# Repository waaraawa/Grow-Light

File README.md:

# Grow Light

A circular 12 V LED board designed for growing plants. The board uses a single-sided, 80 mm aluminum MCPCB with 20 red LEDs and 3 blue LEDs. A [medium Daiso aluminum makgeolli cup](https://www.daisomall.co.kr/pd/pdr/SCR_PDR_0001?pdNo=58656) serves as the heatsink and mechanical structure.

## Project Status

- Current KiCad design: `v1.0.3` (`2026-07-27`)
- Manufacturing order version: `v1.0.2` (`2026-07-11`)
- Current phase: `v1.0.2` assembled, functionally tested, and installed
- `v1.0.3` change: added `F.Silkscreen` guides around the six M3 mounting holes and the central cable hole
- Assembly note: the physical `v1.0.2` board currently uses a temporary hand-assembled resistor arrangement pending replacement with correctly sized `5025 Metric (2010 Imperial)` resistors
- DRC: 0 active errors, 0 active warnings, and 0 unconnected pads
- Exclusion: one warning for the unavailable source library of an embedded silkscreen graphic

> The design files in this repository are currently at `v1.0.3`. The previews below and the ordered MCPCB are `v1.0.2`. Manufacturing files for `v1.0.3` have not been generated.

## Specifications

| Item | Specification |
|---|---|
| PCB | 80 mm diameter, 1-layer Aluminum MCPCB |
| PCB thickness | 1.6 mm |
| Copper | 1 oz, `F.Cu` only |
| Surface finish | `HAL SnPb` |
| Solder mask / silkscreen | White / black, front side only |
| Power input | 12 V from a USB-C PD trigger board |
| Target power consumption | Approximately 2 W to 4 W |
| LEDs | 20 red and 3 blue |
| Resistors | Four 68 Ω and one 82 Ω, 2010 package |
| Track widths | 1.2 mm power tracks and 0.6 mm LED interconnects |
| Mounting holes | Six 3.2 mm M3 NPTH holes |
| Cable hole | One central 5.3 mm NPTH hole |

Because KiCad requires an even number of copper layers, the project represents the stackup as a 2-layer board. All electrical copper is on `F.Cu`; `B.Cu` is unused. The actual manufacturing structure is `F.Silkscreen / F.Mask / F.Cu / thermal dielectric / aluminum base`.

## Electrical Configuration

| Channel | LEDs per Series String | Parallel Strings | Total LEDs | String Resistor |
|---|---:|---:|---:|---:|
| Red | 5 | 4 | 20 | 68 Ω |
| Blue | 3 | 1 | 3 | 82 Ω |

The 2010 resistor bodies act as physical jumpers to complete the single-sided routing. Twenty-four `F.Cu` copper zones around the LEDs provide electrical connectivity and local heat spreading. The aluminum core is the primary thermal path, so the design does not use `B.Cu` heat-spreading copper or thermal vias.

## Design Images

### PCB Layout — v1.0.2

### Manufacturing Preview — v1.0.2

### Assembled Board Preview — v1.0.2

### Manufactured PCB

The physical `v1.0.2` aluminum MCPCB after delivery and initial inspection.

### Completed Assembly

The assembled light installed in its intended growing area.

See the [`v1.0.2` build log](docs/build-log-v1.0.2.md) for the complete assembly, hot-plate reflow, aluminum-cup drilling, thermal-interface, testing, and installation process.

## Assembly and Safety

- The red `IWS-L5056-UR-N3` and blue `IWS-L5056-UB-K3` LEDs use opposite footprint polarities. Verify every LED before placement.
- Do not rely on cable colors. Measure the 12 V output and polarity with a multimeter before soldering the cable to `J1 +12V` and `J2 GND`.
- Fit a grommet or strain relief where the cable passes through the central hole.
- Apply electrically non-conductive `UPSIREN UTP-8` in a thin, even layer between the PCB and the aluminum cup.
- Use insulating washers or nylon shoulder washers at the M3 mounting points.
- Before applying power and again after final assembly, verify that the aluminum structure and fasteners are not shorted to `+12V` or `GND`.
- The aluminum structure and external bracket, rather than the PCB, must carry the lamp's mechanical load.

## Repository Contents

- [`plant led.kicad_sch`](plant%20led.kicad_sch): schematic
- [`plant led.kicad_pcb`](plant%20led.kicad_pcb): PCB layout
- [`plant led.kicad_pro`](plant%20led.kicad_pro): KiCad project settings
- [`parts_list.md`](parts_list.md): parts, manufacturing, and assembly specifications
- [`to-do.md`](to-do.md): production, assembly, and test status
- [`docs/build-log-v1.0.2.md`](docs/build-log-v1.0.2.md): physical `v1.0.2` manufacturing, assembly, and installation log
- [`references/datasheets`](references/datasheets): LED datasheets

Manufacturing Gerber files are not included in the repository. The `footprints:` library is also stored in an external directory shared by multiple projects. To open the project in another environment, configure the same shared library path.

## License

This project is licensed under the [MIT License](LICENSE).

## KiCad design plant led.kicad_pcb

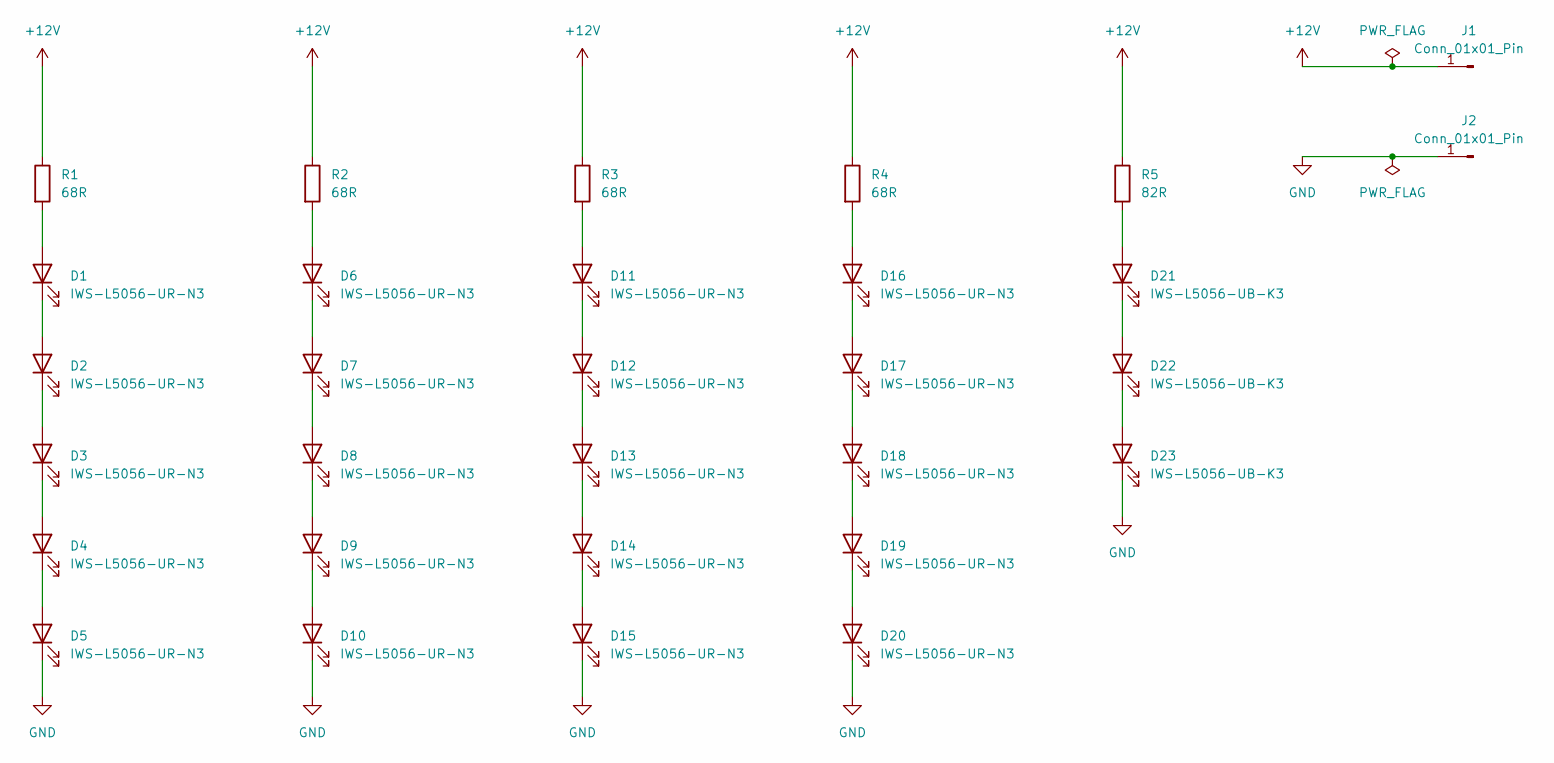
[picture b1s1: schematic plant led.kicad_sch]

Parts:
D1, D2, D3, D4, D5, D6, D7, D8, D9, D10, D11, D12, D13, D14, D15, D16, D17, D18, D19, D20: IWS-L5056-UR-N3; LED_5050_IWS_L5056_UR_N3
D21, D22, D23: IWS-L5056-UB-K3; LED_5050_IWS_L5056_UB_K3
J1, J2: Conn_01x01_Pin; Power_Solder_Pads_1P
R1, R2, R3, R4: 68R; R_2010_5025Metric
R5: 82R; R_2010_5025Metric

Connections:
+12V: J1.1 (Pin_1_1), R1.1, R2.1, R3.1, R4.1, R5.1
GND: D5.1 (K), D10.1 (K), D15.1 (K), D20.1 (K), D23.1 (K), J2.1 (Pin_1_1)
unnamed: D1.2 (A), R1.2
unnamed: D1.1 (K), D2.2 (A)
unnamed: D2.1 (K), D3.2 (A)
unnamed: D3.1 (K), D4.2 (A)
unnamed: D4.1 (K), D5.2 (A)
unnamed: D6.2 (A), R2.2
unnamed: D6.1 (K), D7.2 (A)
unnamed: D7.1 (K), D8.2 (A)
unnamed: D8.1 (K), D9.2 (A)
unnamed: D9.1 (K), D10.2 (A)
unnamed: D11.2 (A), R3.2
unnamed: D11.1 (K), D12.2 (A)
unnamed: D12.1 (K), D13.2 (A)
unnamed: D13.1 (K), D14.2 (A)
unnamed: D14.1 (K), D15.2 (A)
unnamed: D16.2 (A), R4.2
unnamed: D16.1 (K), D17.2 (A)
unnamed: D17.1 (K), D18.2 (A)
unnamed: D18.1 (K), D19.2 (A)
unnamed: D19.1 (K), D20.2 (A)
unnamed: D21.2 (A), R5.2
unnamed: D21.1 (K), D22.2 (A)
unnamed: D22.1 (K), D23.2 (A)

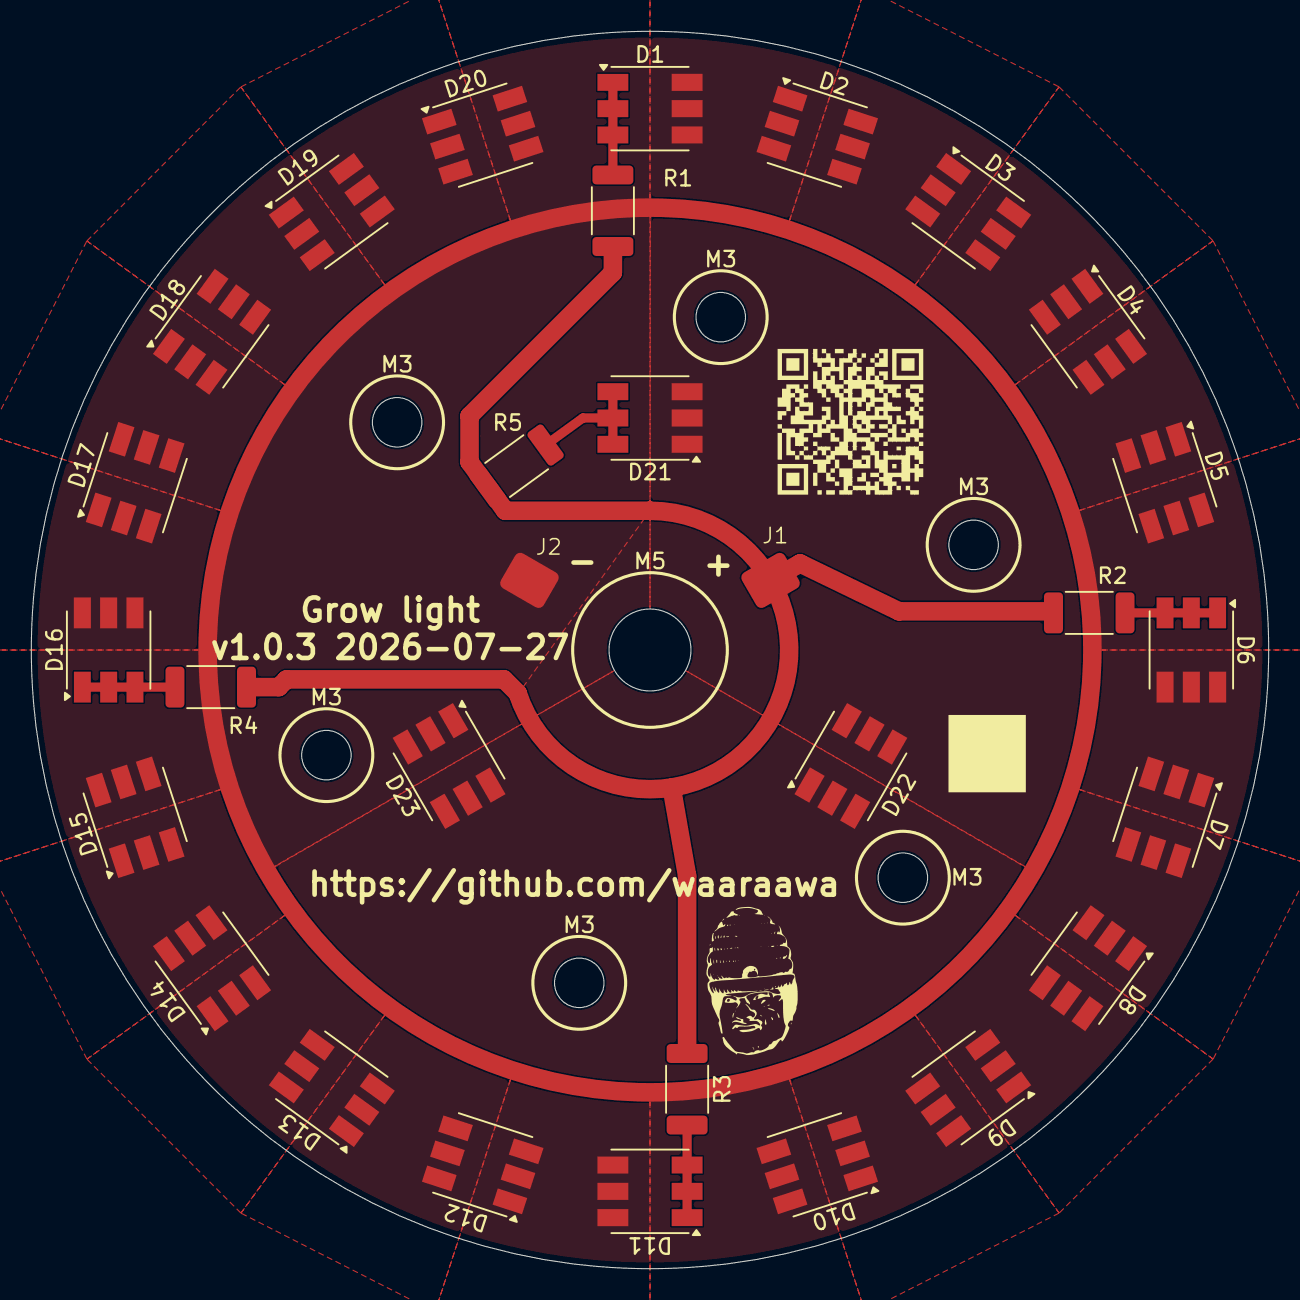
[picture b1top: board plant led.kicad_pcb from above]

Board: 2 copper layers, 80.0 x 80.0 mm, 37 parts (0 on the bottom side), 25 nets.

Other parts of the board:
M3, M3#2, M3#3, M3#4, M3#5, M3#6: MountingHole_3.2mm_M3_DIN965
M5: MountingHole_5.3mm_M5_DIN965
